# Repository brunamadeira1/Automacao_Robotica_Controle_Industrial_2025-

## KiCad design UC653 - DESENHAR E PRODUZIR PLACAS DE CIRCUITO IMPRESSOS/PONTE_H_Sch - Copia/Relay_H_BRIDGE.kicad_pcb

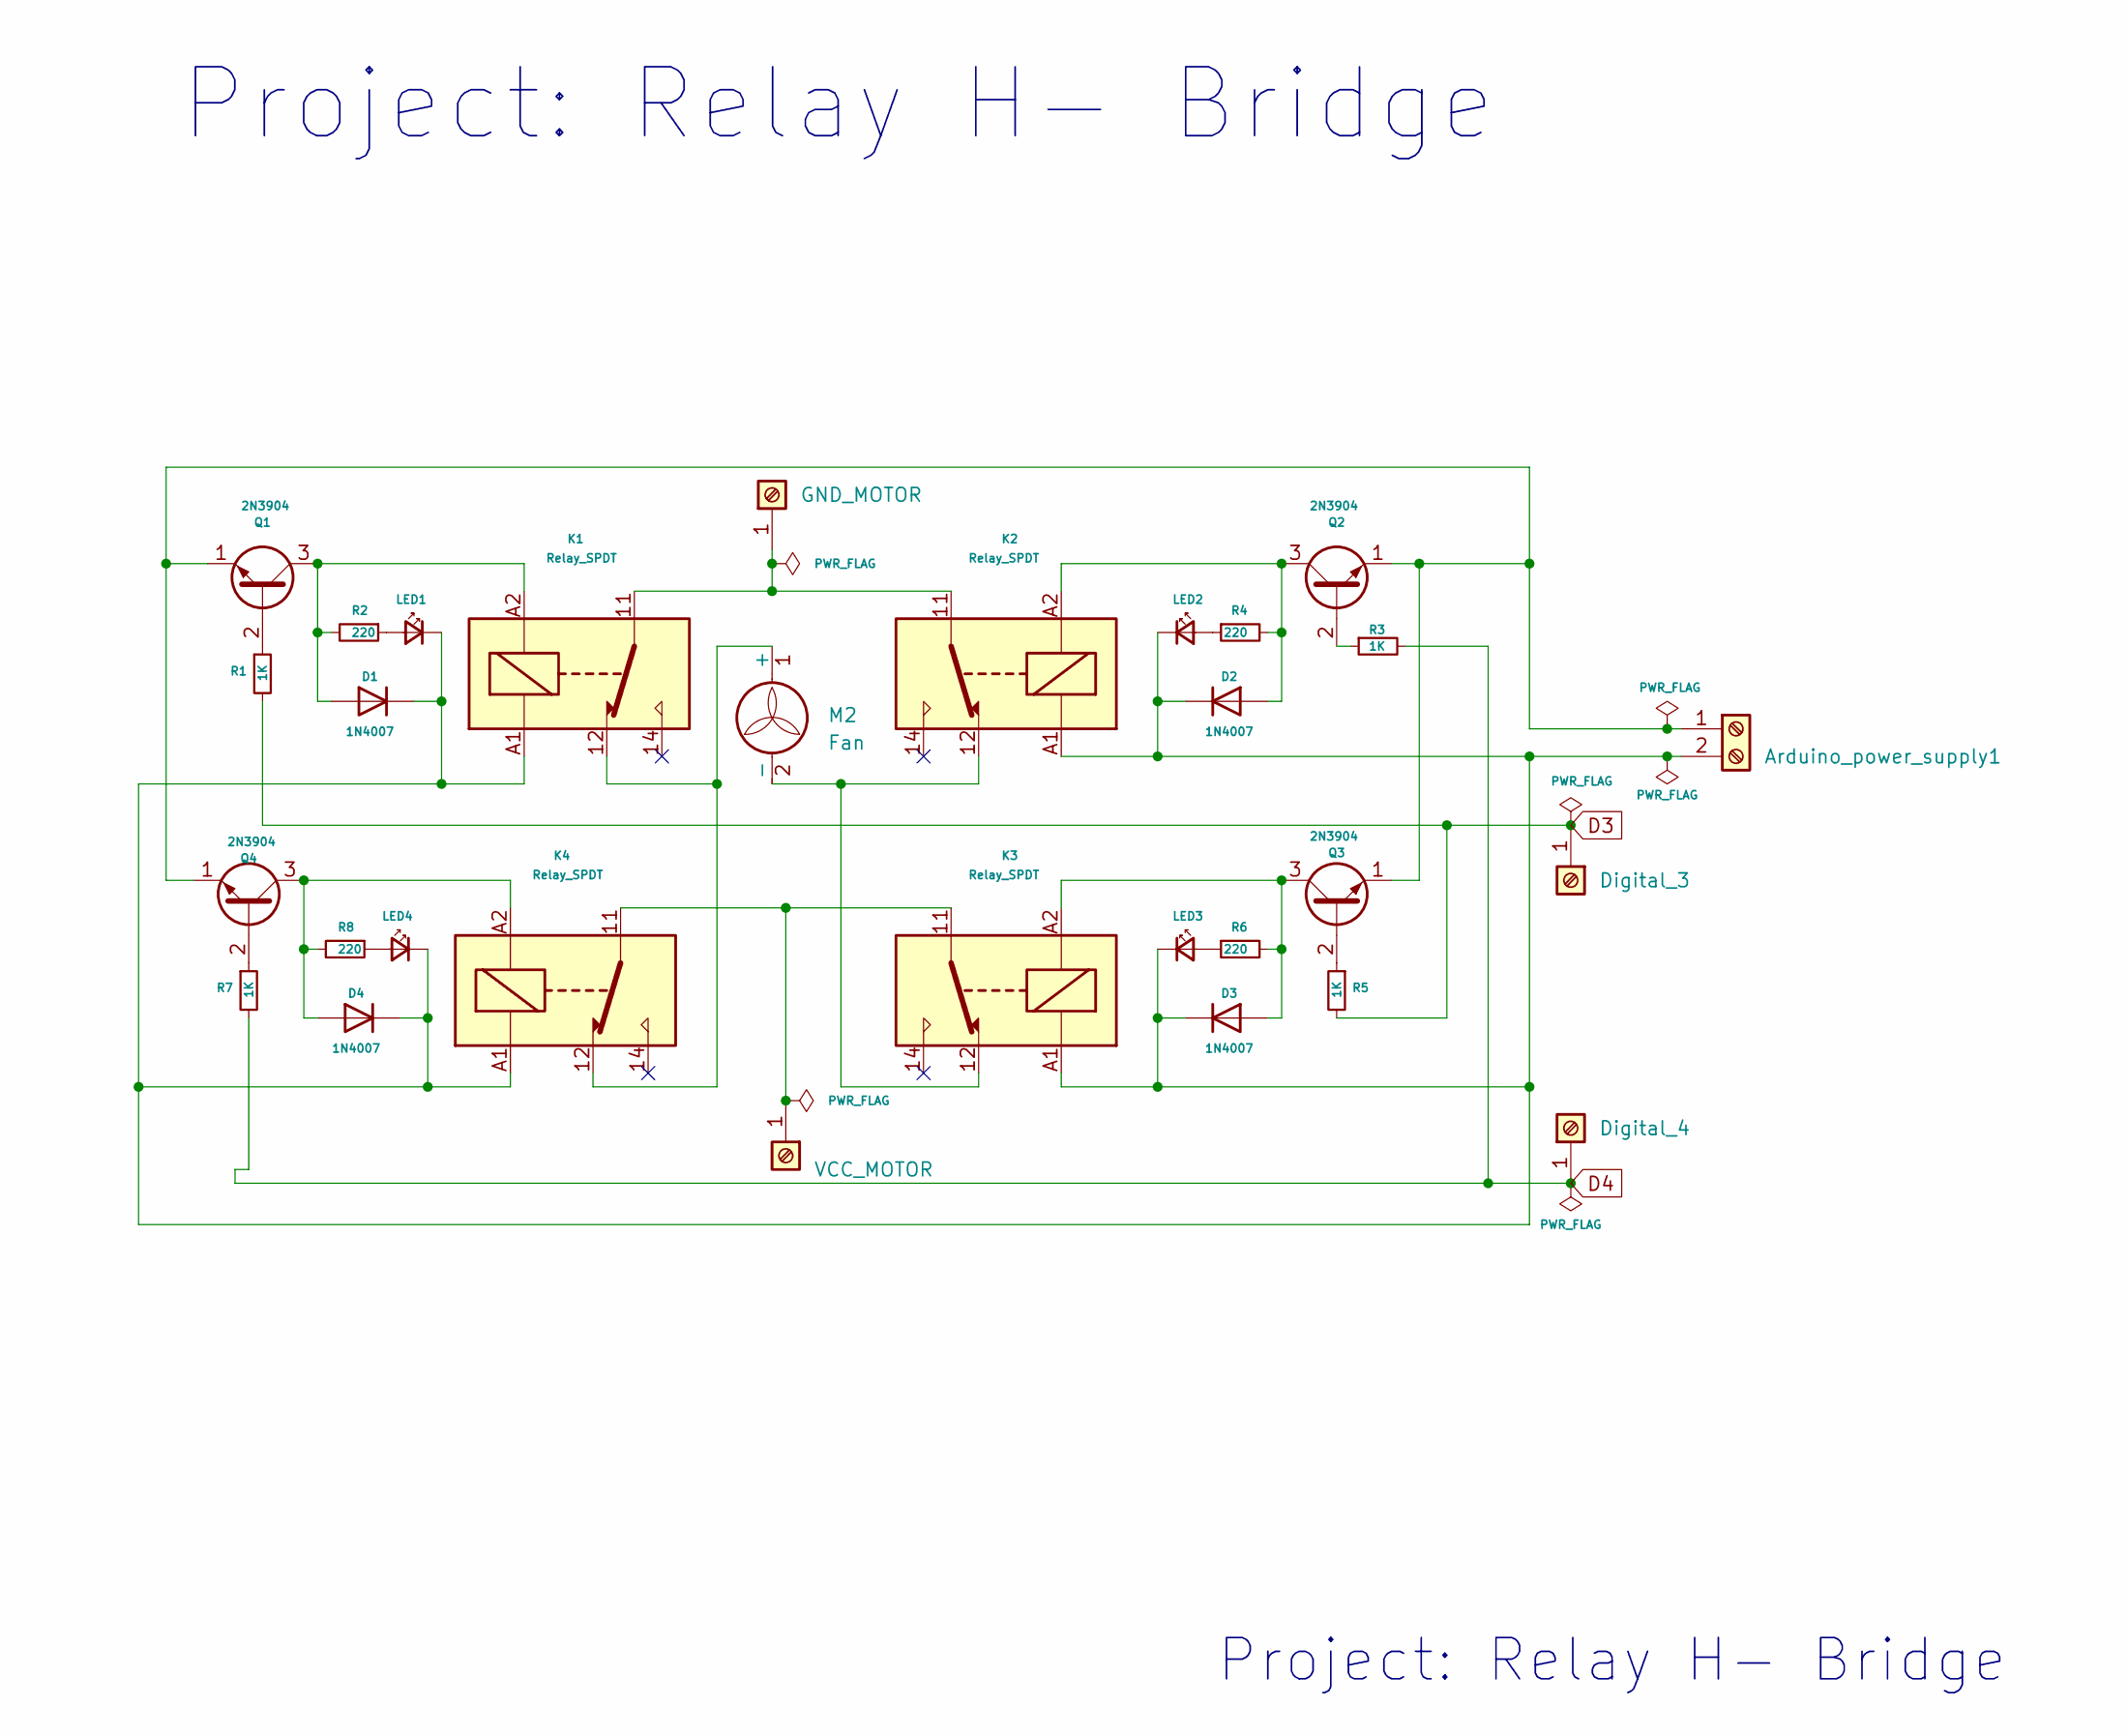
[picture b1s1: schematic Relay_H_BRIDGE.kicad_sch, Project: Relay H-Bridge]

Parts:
Arduino_power_supply1: Arduino_power_supply1; PhoenixContact_GMSTBA_2,5_2-G-7,62_1x02_P7.62mm_Horizontal
D1, D2, D3, D4: 1N4007; D_DO-41_SOD81_P10.16mm_Horizontal
Digital_3: Digital_3; PhoenixContact_SPT_2.5_1-H-5.0_1x01_P5.0mm_Horizontal
Digital_4: Digital_4; PhoenixContact_SPT_2.5_1-H-5.0_1x01_P5.0mm_Horizontal
GND1: GND_MOTOR; PhoenixContact_SPT_2.5_1-H-5.0_1x01_P5.0mm_Horizontal
K1, K2, K3, K4: Relay_SPDT; Relay_SPDT_Schrack-RT1-FormC_RM5mm
LED1, LED2, LED3, LED4: LED_Small; LED_D3.0mm
M2: Fan; PhoenixContact_GMSTBA_2,5_2-G-7,62_1x02_P7.62mm_Horizontal
Q1, Q2, Q3, Q4: 2N3904; TO-92_Inline
R1, R3, R5, R7: 1K; R_Axial_DIN0207_L6.3mm_D2.5mm_P7.62mm_Horizontal
R2, R4, R6, R8: 220; R_Axial_DIN0207_L6.3mm_D2.5mm_P7.62mm_Horizontal
VCC_MOTOR1: VCC_MOTOR; PhoenixContact_SPT_2.5_1-H-5.0_1x01_P5.0mm_Horizontal

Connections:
D3: Digital_3.1, R1.2, R5.2
D4: Digital_4.1, R3.2, R7.2
unnamed: Arduino_power_supply1.1, Q1.1 (E), Q2.1 (E), Q3.1 (E), Q4.1 (E)
unnamed: Arduino_power_supply1.2, D1.1 (K), D2.1 (K), D3.1 (K), D4.1 (K), K1.A1, K2.A1, K3.A1, K4.A1, LED1.1 (K), LED2.1 (K), LED3.1 (K), LED4.1 (K)
unnamed: D1.2 (A), K1.A2, Q1.3 (C), R2.2
unnamed: D2.2 (A), K2.A2, Q2.3 (C), R4.2
unnamed: D3.2 (A), K3.A2, Q3.3 (C), R6.2
unnamed: D4.2 (A), K4.A2, Q4.3 (C), R8.2
unnamed: GND1.1, K1.11, K2.11
unnamed: LED1.2 (A), R2.1
unnamed: LED2.2 (A), R4.1
unnamed: LED3.2 (A), R6.1
unnamed: LED4.2 (A), R8.1
unnamed: K1.12, K4.12, M2.1 (+)
unnamed: K2.12, K3.12, M2.2 (-)
unnamed: Q1.2 (B), R1.1
unnamed: Q2.2 (B), R3.1
unnamed: Q3.2 (B), R5.1
unnamed: Q4.2 (B), R7.1
unnamed: K3.11, K4.11, VCC_MOTOR1.1

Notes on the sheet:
Project: Relay H- Bridge

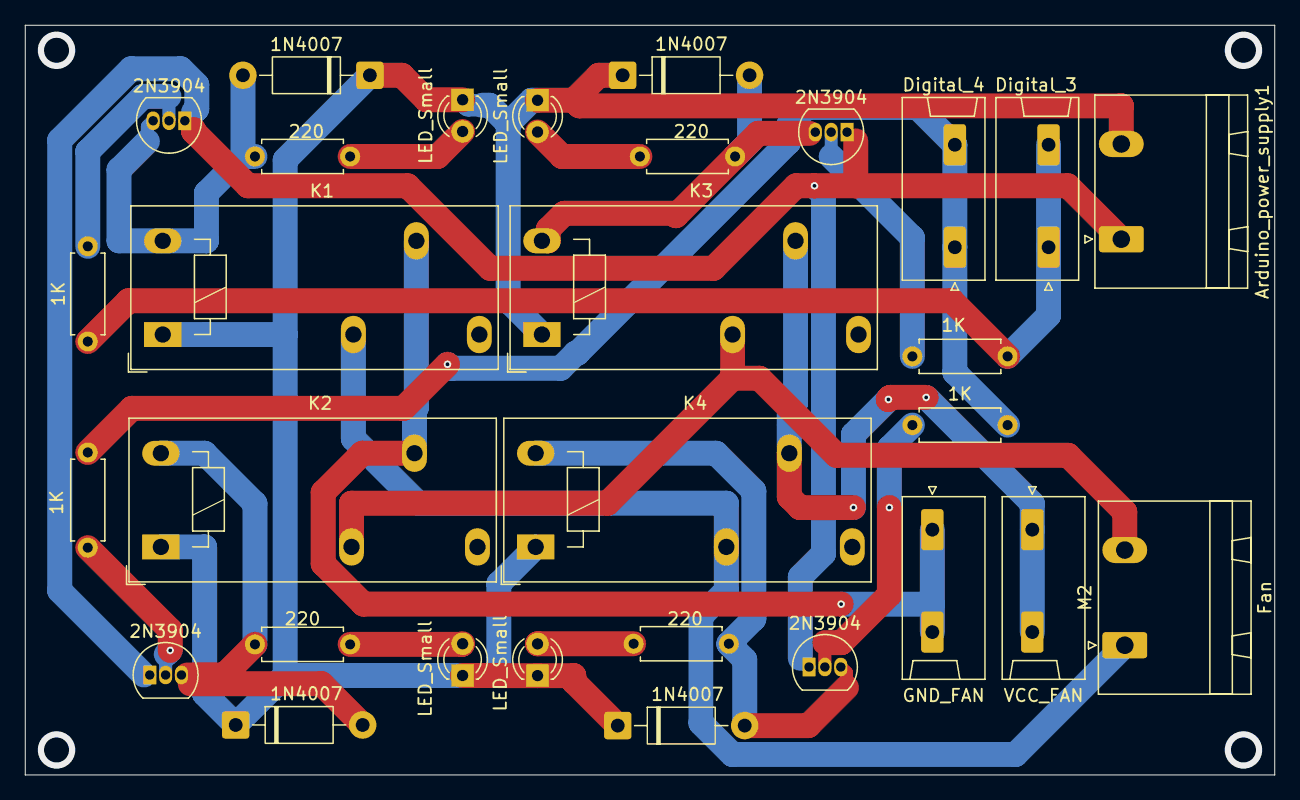
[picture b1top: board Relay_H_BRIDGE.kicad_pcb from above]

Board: 2 copper layers, 100.0 x 60.0 mm, 30 parts (0 on the bottom side), 20 nets.

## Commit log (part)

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2026-03-05 UC670_EFETUAR_A_PROGRAMACAO_DE_MICROCONTROLADORES/SESSAO_10_10_2025/ESQUEMA ELETRONICO/Projeto_1LED.pdf
